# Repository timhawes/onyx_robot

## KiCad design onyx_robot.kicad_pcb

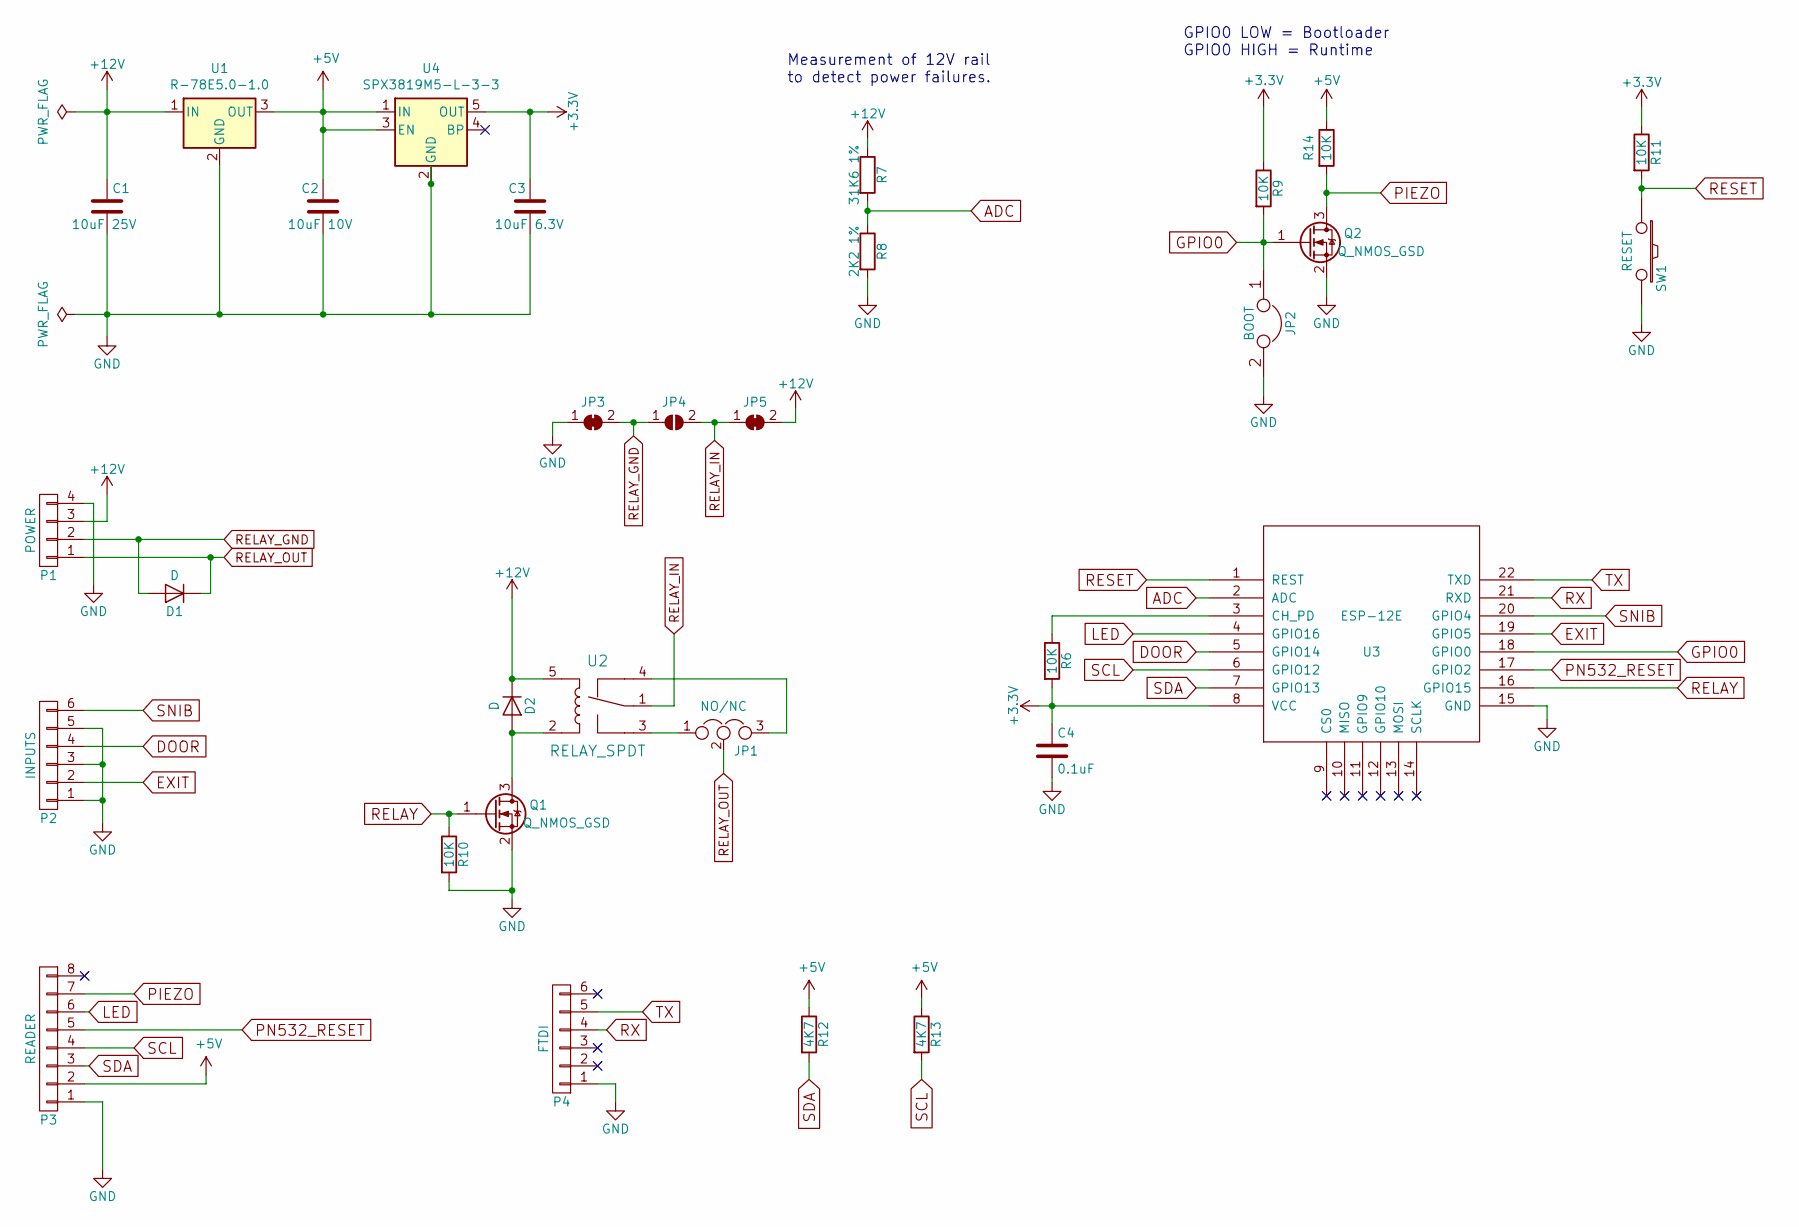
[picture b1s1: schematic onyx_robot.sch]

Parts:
C1: 10uF 25V; C_0805_2012Metric
C2: 10uF 10V; C_0805_2012Metric
C3: 10uF 6.3V; C_0805_2012Metric
C4: 0.1uF; C_0603_1608Metric
D1, D2: D; D_SMA
JP1: NO/NC; PinHeader_1x03_P2.54mm_Vertical
JP2: BOOT; PinHeader_1x02_P2.54mm_Vertical
JP3, JP5: SolderJumper_2_Bridged; SolderJumper-2_P1.3mm_Bridged_RoundedPad1.0x1.5mm
JP4: SolderJumper_2_Open; SolderJumper-2_P1.3mm_Open_RoundedPad1.0x1.5mm
P1: POWER; Terminal_Block_5.08mm_x4
P2: INPUTS; Terminal_Block_5.08mm_x6
P3: READER; Terminal_Block_5.08mm_x8
P4: FTDI; Pin_Header_Straight_1x06
Q1, Q2: Q_NMOS_GSD; SOT-23
R6, R9, R10, R11, R14: 10K; R_0603_1608Metric
R7: 31K6 1%; R_0603_1608Metric
R8: 2K2 1%; R_0603_1608Metric
R12, R13: 4K7; R_0603_1608Metric
SW1: RESET; EVQPT5
U1: R-78E5.0-1.0; Converter_DCDC_RECOM_R-78E-0.5_THT
U2: RELAY_SPDT; JS_RELAY
U3: ESP-12E
U4: SPX3819M5-L-3-3; SOT-23-5

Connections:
+3V3: C3.1, C4.1, R6.2, R9.1, R11.1, U3.8 (VCC), U4.5 (OUT)
+5V: C2.1, P3.2, R12.1, R13.1, R14.1, U1.3 (OUT), U4.1 (IN), U4.3 (EN)
+12V: C1.1, D2.1 (K), JP5.2 (B), P1.3, R7.1, U1.1 (IN), U2.5
ADC: R7.2, R8.1, U3.2 (ADC)
DOOR: P2.4, U3.5 (GPIO14)
EXIT: P2.2, U3.19 (GPIO5)
GND: C1.2, C2.2, C3.2, C4.2, JP2.2, JP3.1 (A), P1.4, P2.1, P2.3, P2.5, P3.1, P4.1, Q1.2 (S), Q2.2 (S), R8.2, R10.2, SW1.2, U1.2 (GND), U3.15 (GND), U4.2 (GND)
GPIO0: JP2.1, Q2.1 (G), R9.2, U3.18 (GPIO0)
LED: P3.6, U3.4 (GPIO16)
unnamed: D2.2 (A), Q1.3 (D), U2.2
unnamed: JP1.1, U2.3
unnamed: JP1.3, U2.4
unnamed: R6.1, U3.3 (CH_PD)
PIEZO: P3.7, Q2.3 (D), R14.2
PN532_RESET: P3.5, U3.17 (GPIO2)
RELAY: Q1.1 (G), R10.1, U3.16 (GPIO15)
RELAY_GND: D1.2 (A), JP3.2 (B), JP4.1 (A), P1.2
RELAY_IN: JP4.2 (B), JP5.1 (A), U2.1
RELAY_OUT: D1.1 (K), JP1.2, P1.1
RESET: R11.2, SW1.1, U3.1 (REST)
RX: P4.4, U3.21 (RXD)
SCL: P3.4, R13.2, U3.6 (GPIO12)
SDA: P3.3, R12.2, U3.7 (GPIO13)
SNIB: P2.6, U3.20 (GPIO4)
TX: P4.5, U3.22 (TXD)

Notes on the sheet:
Measurement of 12V rail to detect power failures.
GPIO0 LOW = Bootloader GPIO0 HIGH = Runtime

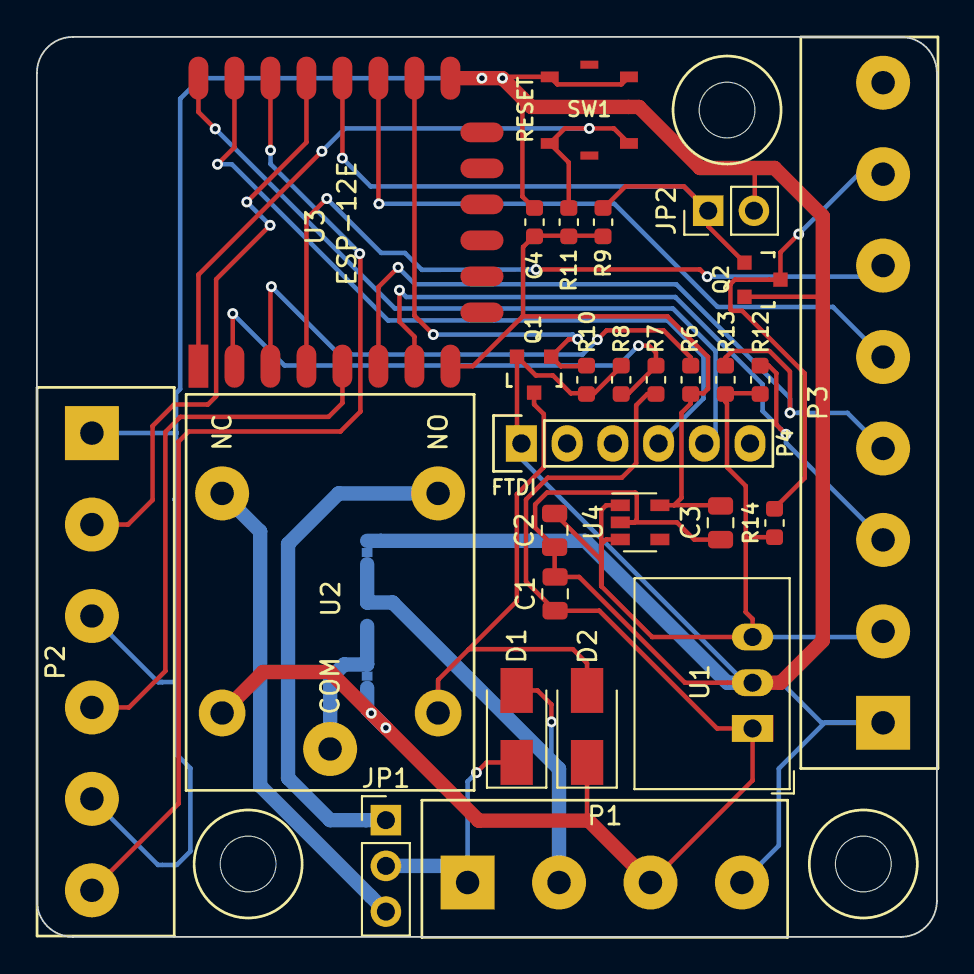
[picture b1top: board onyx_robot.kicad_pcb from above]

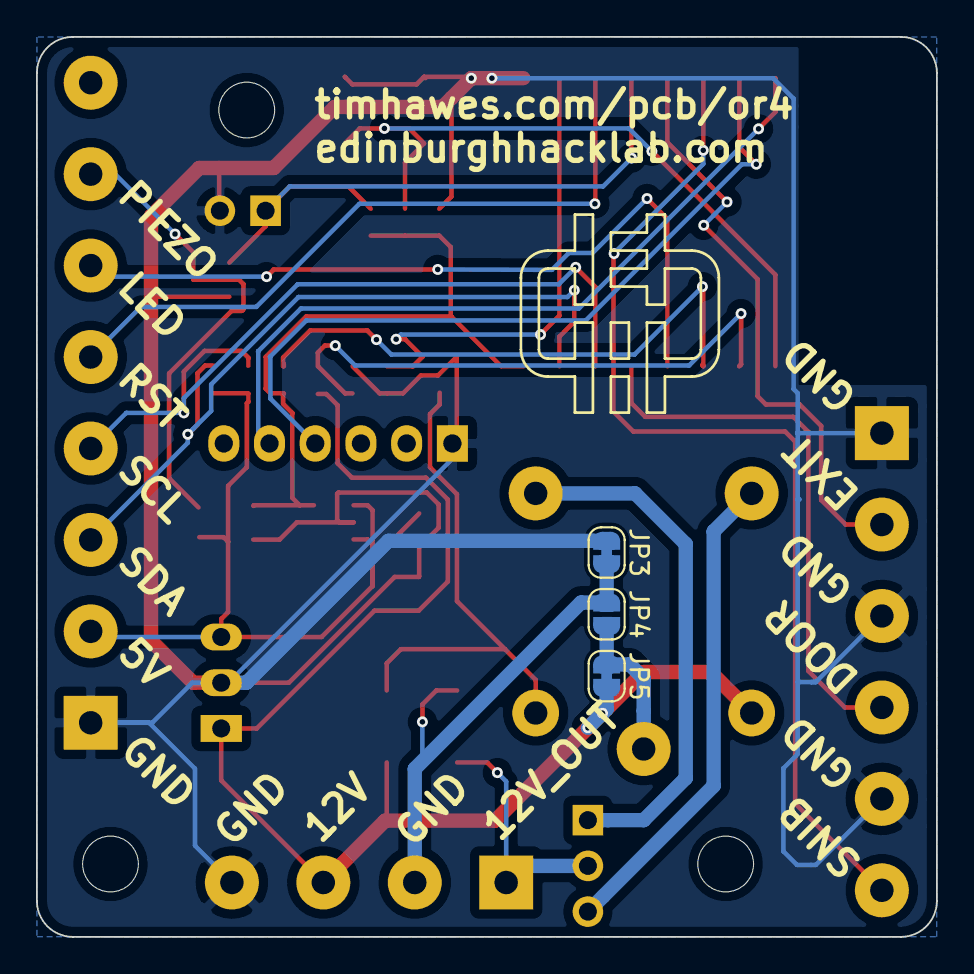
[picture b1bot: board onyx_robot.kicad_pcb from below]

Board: 2 copper layers, 50.0 x 50.0 mm, 31 parts (3 on the bottom side), 25 nets.

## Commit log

2015-06-20 Add decoupling capacitor to ESP8266 and optional snib/tamper outputs
2015-06-20 Option to add more power supply capacitors later
2015-06-20 Remove stray junction
2015-06-20 New component for relay, pin numbering consistent with intended footprint
2015-06-24 Assign footprints
2015-06-26 FET and jumper added to piezo output Fix to incorrect net connection in power supply Connectors rearranged to 8+6+6 configuration Footprints assigned
2015-06-27 Move SNIB closer to the ESP
2015-06-27 Swap 12V in/out connector pins
2015-06-28 Switch to standard (not hand-soldering) footprints to save space
2015-06-28 Use corrected ESP-12E footprint
2015-06-28 Shuffle READER pins to put GND/3.3V together
2015-06-29 Swap power in/out pins
2015-06-29 PCB checked-in
2015-06-30 Tidy-ups, increase track size
2015-07-01 Text tidied-up. Relay repositioned to give larger gaps. Mounting holes enlarged.
2015-07-01 Restore FTDI reference text
2015-07-01 Gerbers added
2015-07-01 PDF regenerated
2015-07-01 Clean-up silkscreen labels
2015-07-02 Change MOSFET SOT-23 pin ordering and adjust layout to match
2015-07-03 Increased clearance between Q2 and screw terminals
2015-08-18 Correction to value of R2
2015-08-18 Change ADC voltage divider to match the 0-1V ADC requirement
2015-08-18 Swap RX/TX on FTDI header
2015-08-18 Fix RX/TX in PCB and regenerate all files
2015-08-21 Version 2
2015-08-30 Finished version 2
2019-08-02 Revision 3
    Off-the-shelf power supply module
    5V supplied to NFC reader
    Piezo improved
    ESD protection removed to complexity
    NC contact removed from relay
    VCC removed from FTDI connector
2019-08-03 Remove stale netlist file
2019-09-21 Changes to text
2020-07-13 Revision 4
2020-07-18 No volt relay option
